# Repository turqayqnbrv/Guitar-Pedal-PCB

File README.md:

# Guitar-Pedal-PCB
This is a project repository for distortion pedal desgined with KiCAD

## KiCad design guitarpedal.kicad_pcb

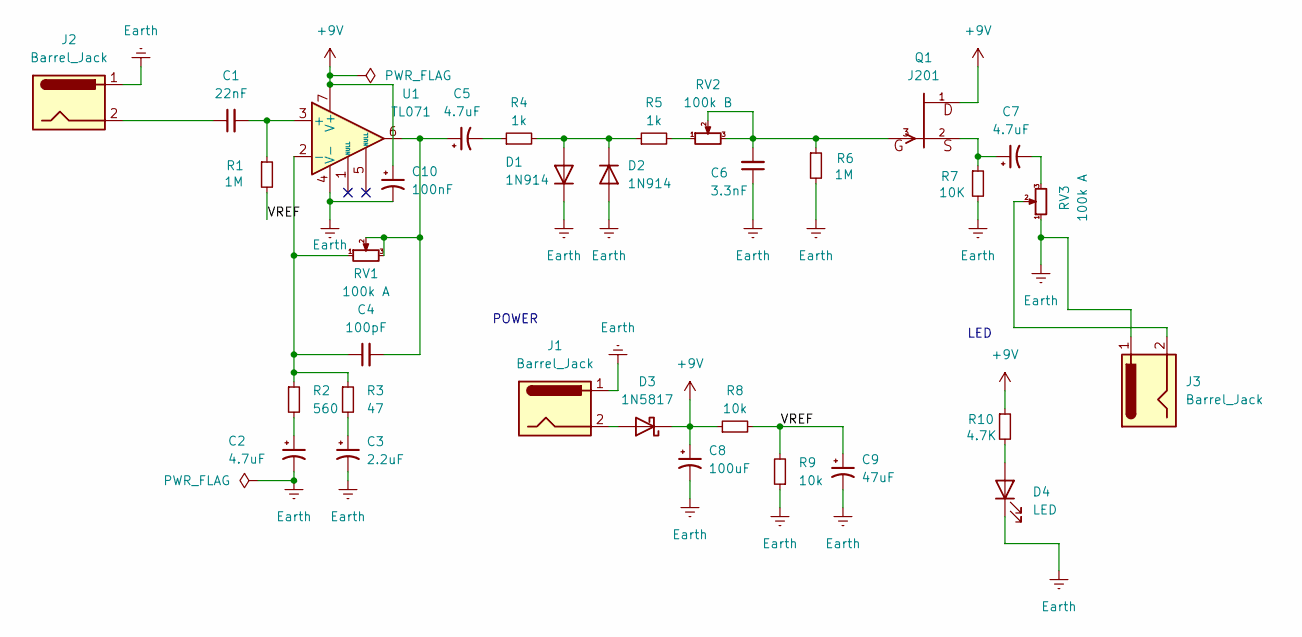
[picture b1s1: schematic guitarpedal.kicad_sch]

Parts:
C1: 22nF; C_Rect_L7.2mm_W2.5mm_P5.00mm_FKS2_FKP2_MKS2_MKP2
C2, C5, C7: 4.7uF; C_Radial_D5.0mm_H7.0mm_P2.00mm
C3: 2.2uF; C_Radial_D5.0mm_H7.0mm_P2.00mm
C4: 100pF; C_Disc_D5.0mm_W2.5mm_P5.00mm
C6: 3.3nF; C_Rect_L7.2mm_W2.5mm_P5.00mm_FKS2_FKP2_MKS2_MKP2
C8: 100uF; C_Radial_D6.3mm_H7.0mm_P2.50mm
C9: 47uF; C_Radial_D5.0mm_H7.0mm_P2.00mm
C10: 100nF; C_Disc_D5.0mm_W2.5mm_P5.00mm
D1, D2: 1N914; D_DO-35_SOD27_P7.62mm_Horizontal
D3: 1N5817; D_DO-41_SOD81_P10.16mm_Horizontal
D4: LED; LED_D5.0mm
J1, J2, J3: Barrel_Jack; BarrelJack_Horizontal
Q1: J201; TO-92L_Inline_Wide; MPN J201
R1, R6: 1M; R_Axial_DIN0207_L6.3mm_D2.5mm_P7.62mm_Horizontal
R2: 560; R_Axial_DIN0207_L6.3mm_D2.5mm_P7.62mm_Horizontal
R3: 47; R_Axial_DIN0207_L6.3mm_D2.5mm_P7.62mm_Horizontal
R4, R5: 1k; R_Axial_DIN0207_L6.3mm_D2.5mm_P7.62mm_Horizontal
R7: 10K; R_Axial_DIN0207_L6.3mm_D2.5mm_P7.62mm_Horizontal
R8, R9: 10k; R_Axial_DIN0207_L6.3mm_D2.5mm_P7.62mm_Horizontal
R10: 4.7K; R_Axial_DIN0207_L6.3mm_D2.5mm_P7.62mm_Horizontal
RV1, RV3: 100k A; Pot_Alpha_RV16AF-42_100K
RV2: 100k B; Pot_Alpha_RV16AF-42_100K
U1: TL071; DIP-8_W7.62mm

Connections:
+9V: C8.1, C10.1, D3.1 (K), Q1.1, R8.1, R10.1, U1.7 (V+)
/VREF: C9.1, R1.2, R8.2, R9.2
Earth: C2.2, C3.2, C6.1, C8.2, C9.2, C10.2, D1.1 (K), D2.2 (A), D4.1 (K), J1.1, J2.1, J3.1, R6.2, R7.2, R9.1, RV3.1, U1.4 (V-)
unnamed: C1.1, J2.2
unnamed: C2.1, R2.2
unnamed: C3.1, R3.2
unnamed: C4.2, C5.1, RV1.2, RV1.3, U1.6
unnamed: C5.2, R4.1
unnamed: C6.2, Q1.3, R6.1, RV2.2, RV2.3
unnamed: C7.1, Q1.2, R7.1
unnamed: C7.2, RV3.3
unnamed: D1.2 (A), D2.1 (K), R4.2, R5.1
unnamed: D3.2 (A), J1.2
unnamed: D4.2 (A), R10.2
unnamed: J3.2, RV3.2
unnamed: R5.2, RV2.1
unnamed: C1.2, R1.1, U1.3 (+)
unnamed: C4.1, R2.1, R3.1, RV1.1, U1.2 (-)

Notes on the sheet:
LED
POWER

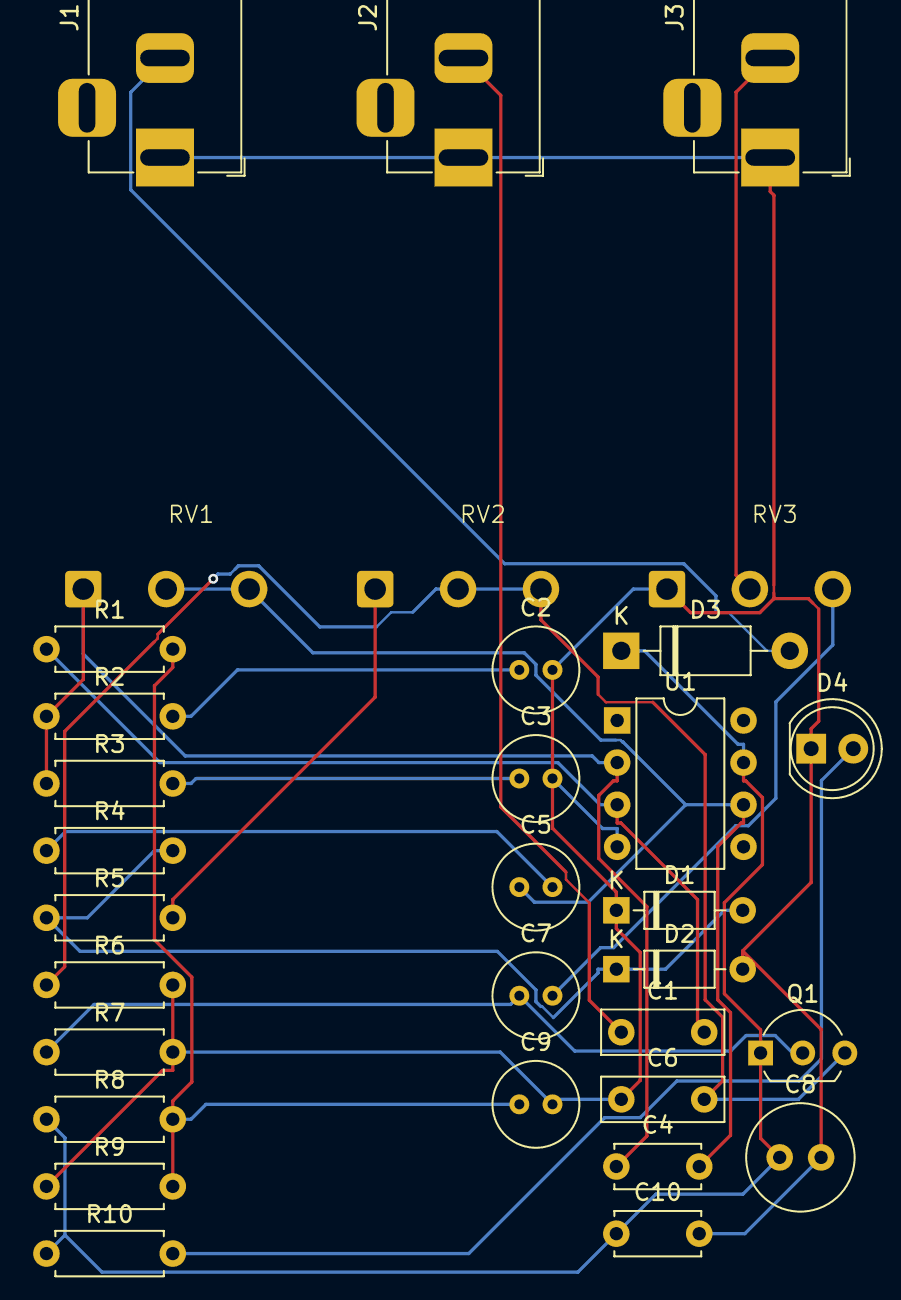
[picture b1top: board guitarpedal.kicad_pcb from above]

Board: 2 copper layers, 32 parts (0 on the bottom side), 18 nets.
